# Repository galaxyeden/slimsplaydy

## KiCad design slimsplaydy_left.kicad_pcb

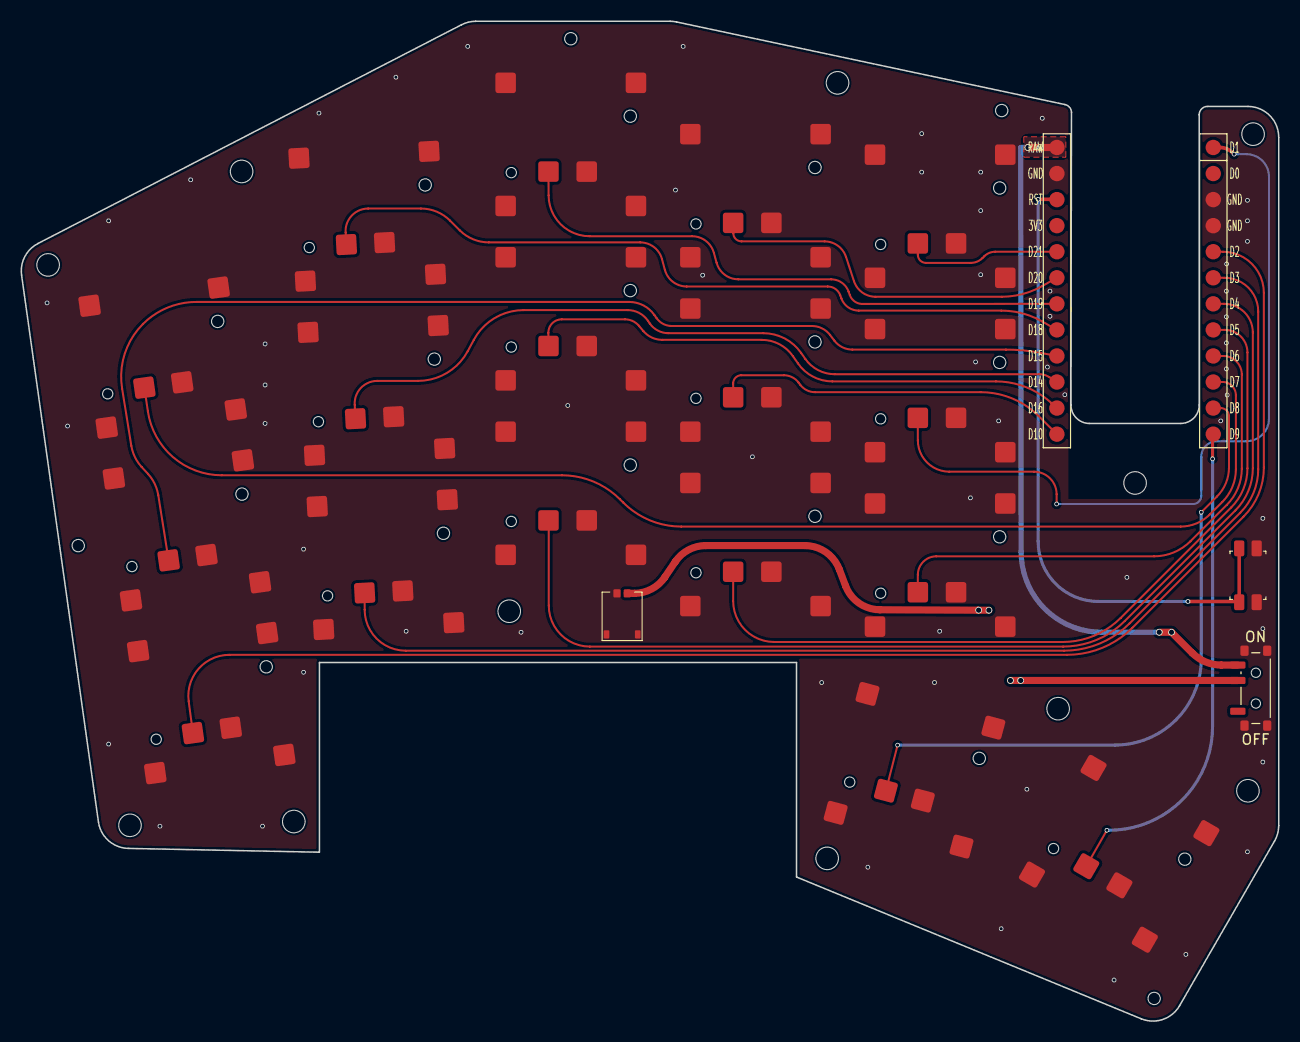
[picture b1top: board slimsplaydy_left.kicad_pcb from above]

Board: 2 copper layers, 122.6 x 97.5 mm, 37 parts (1 on the bottom side), 21 nets.

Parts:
CONN1: Battery Connector; Molex_Pico_EZMate_Plus_1x02
MAG1: magsafe
MCU1: nice_nano; mcu_nice_nano
MH1, MH2, MH3, MH4, MH5, MH6, MH7, MH8, MH9, MH10, MH11, MH12, MH13, MH14, MH15: mounting_hole_npth
PWR1: Power SW; power_switch_smd_side
RST1: Reset SW; reset_switch_smd_side
S1, S2, S3, S4, S5, S6, S7, S8, S9, S10, S11, S12, S13, S14, S15, S16, S17: PG1316S

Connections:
BAT_P: CONN1.2, PWR1.2 (B)
GND: CONN1.1, CONN1.MP (MountPin), MCU1.3 (GND), MCU1.4 (GND), MCU1.23 (GND), PWR1.MP, RST1.1, RST1.3, S1.2, S1.3 (B), S2.2, S2.3 (B), S3.2, S3.3 (B), S4.2, S4.3 (B), S5.2, S5.3 (B), S6.2, S6.3 (B), S7.2, S7.3 (B), S8.2, S8.3 (B), S9.2, S9.3 (B), S10.2, S10.3 (B), S11.2, S11.3 (B), S12.2, S12.3 (B), S13.2, S13.3 (B), S14.2, S14.3 (B), S15.2, S15.3 (B), S16.2, S16.3 (B), S17.2, S17.3 (B)
RAW: MCU1.24 (BAT+), PWR1.3 (C)
RST: MCU1.22 (RST), RST1.2, RST1.4
finger_index_bottom: MCU1.8 (P0.24), S10.1
finger_index_home: MCU1.13 (P0.09-LF), S11.1
finger_index_top: MCU1.19 (P0.29-LF), S12.1
finger_inner_bottom: MCU1.9 (P1.00), S13.1
finger_inner_home: MCU1.1 (P0.06), S14.1
finger_inner_top: MCU1.20 (P0.31-LF), S15.1
finger_middle_bottom: MCU1.7 (P0.22), S7.1
finger_middle_home: MCU1.14 (P0.10-LF), S8.1
finger_middle_top: MCU1.18 (P0.02-LF), S9.1
finger_pinky_bottom: MCU1.5 (P0.17), S1.1
finger_pinky_home: MCU1.16 (P1.13-LF), S2.1
finger_pinky_top: MCU1.10 (P0.11), S3.1
finger_ring_bottom: MCU1.6 (P0.20), S4.1
finger_ring_home: MCU1.15 (P1.11-LF), S5.1
finger_ring_top: MCU1.17 (P1.15-LF), S6.1
thumb_reachy_fan: MCU1.12 (P1.06-LF), S17.1
thumb_tucky_fan: MCU1.11 (P1.04-LF), S16.1

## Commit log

2025-06-13 some ideas and how-tos
2025-06-13 fixed cutout
2025-06-13 removed stray extension log not in repo gitignore
2025-06-13 rerouted tracks, stitched ground, fixed footprints, fixed mcu clearance
2025-06-13 silly gitignore needed
